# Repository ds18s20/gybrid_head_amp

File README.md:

# gybrid_head_amp
headphone amplifier using vacuum tube  and transistor in class A

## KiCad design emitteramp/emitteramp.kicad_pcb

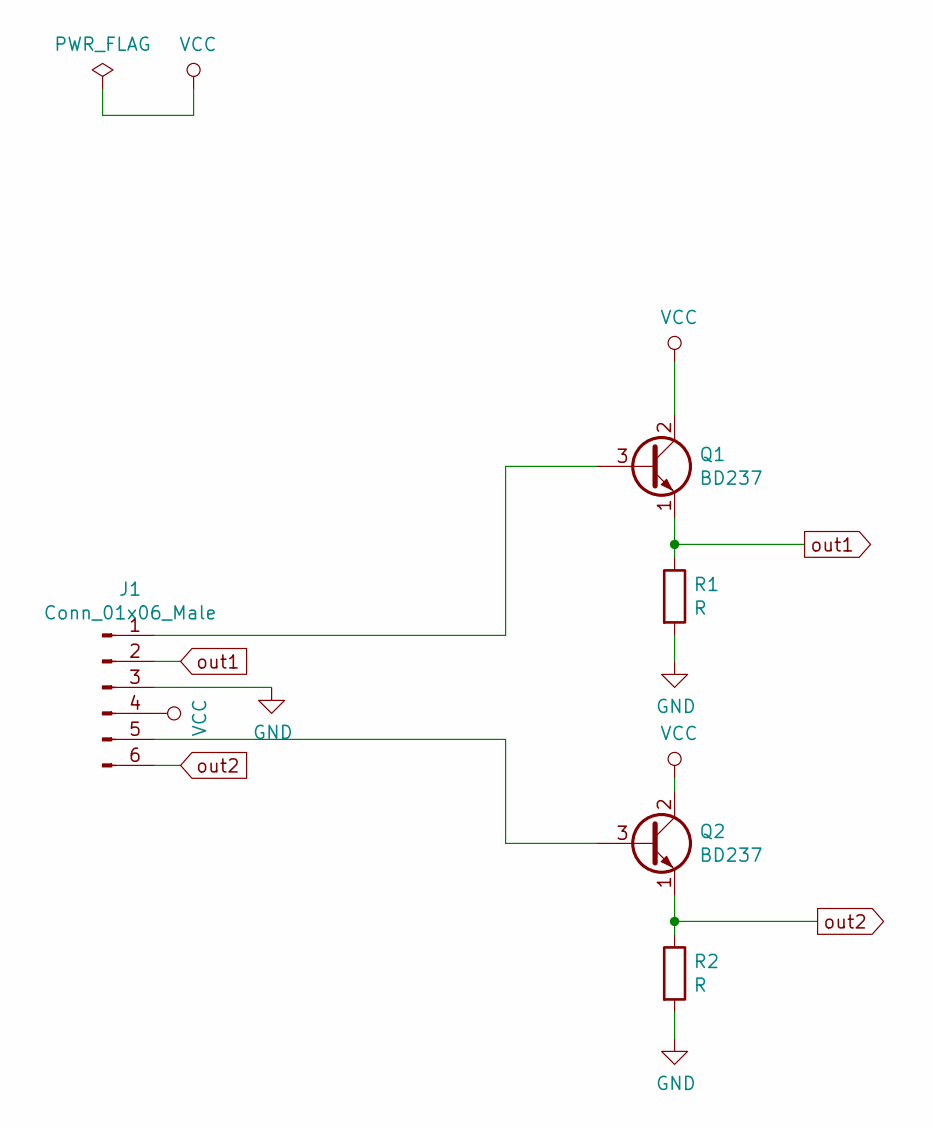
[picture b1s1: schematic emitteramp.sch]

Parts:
J1: Conn_01x06_Male; MyConn1x6
Q1, Q2: BD237; TO-126-3_Horizontal_TabDown
R1, R2: R; R_Axial_DIN0516_L15.5mm_D5.0mm_P20.32mm_Horizontal

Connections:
GND: J1.3, R1.2, R2.2
unnamed: J1.1, Q1.3 (B)
unnamed: J1.5, Q2.3 (B)
VCC: J1.4, Q1.2 (C), Q2.2 (C)
out1: J1.2, Q1.1 (E), R1.1
out2: J1.6, Q2.1 (E), R2.1

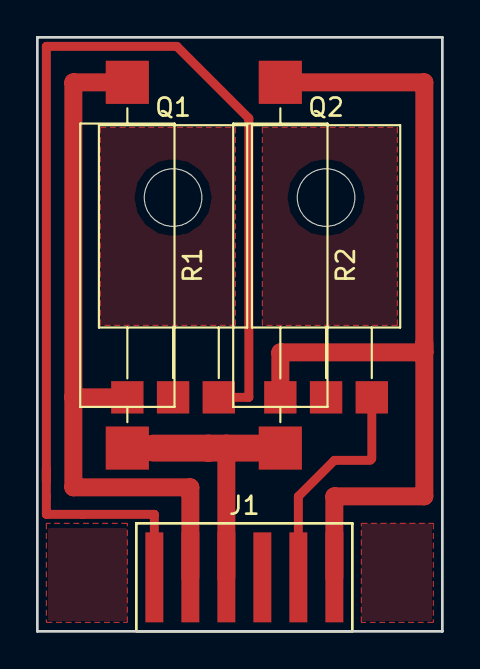
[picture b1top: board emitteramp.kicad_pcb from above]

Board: 2 copper layers, 22.5 x 33.0 mm, 5 parts (0 on the bottom side), 6 nets.

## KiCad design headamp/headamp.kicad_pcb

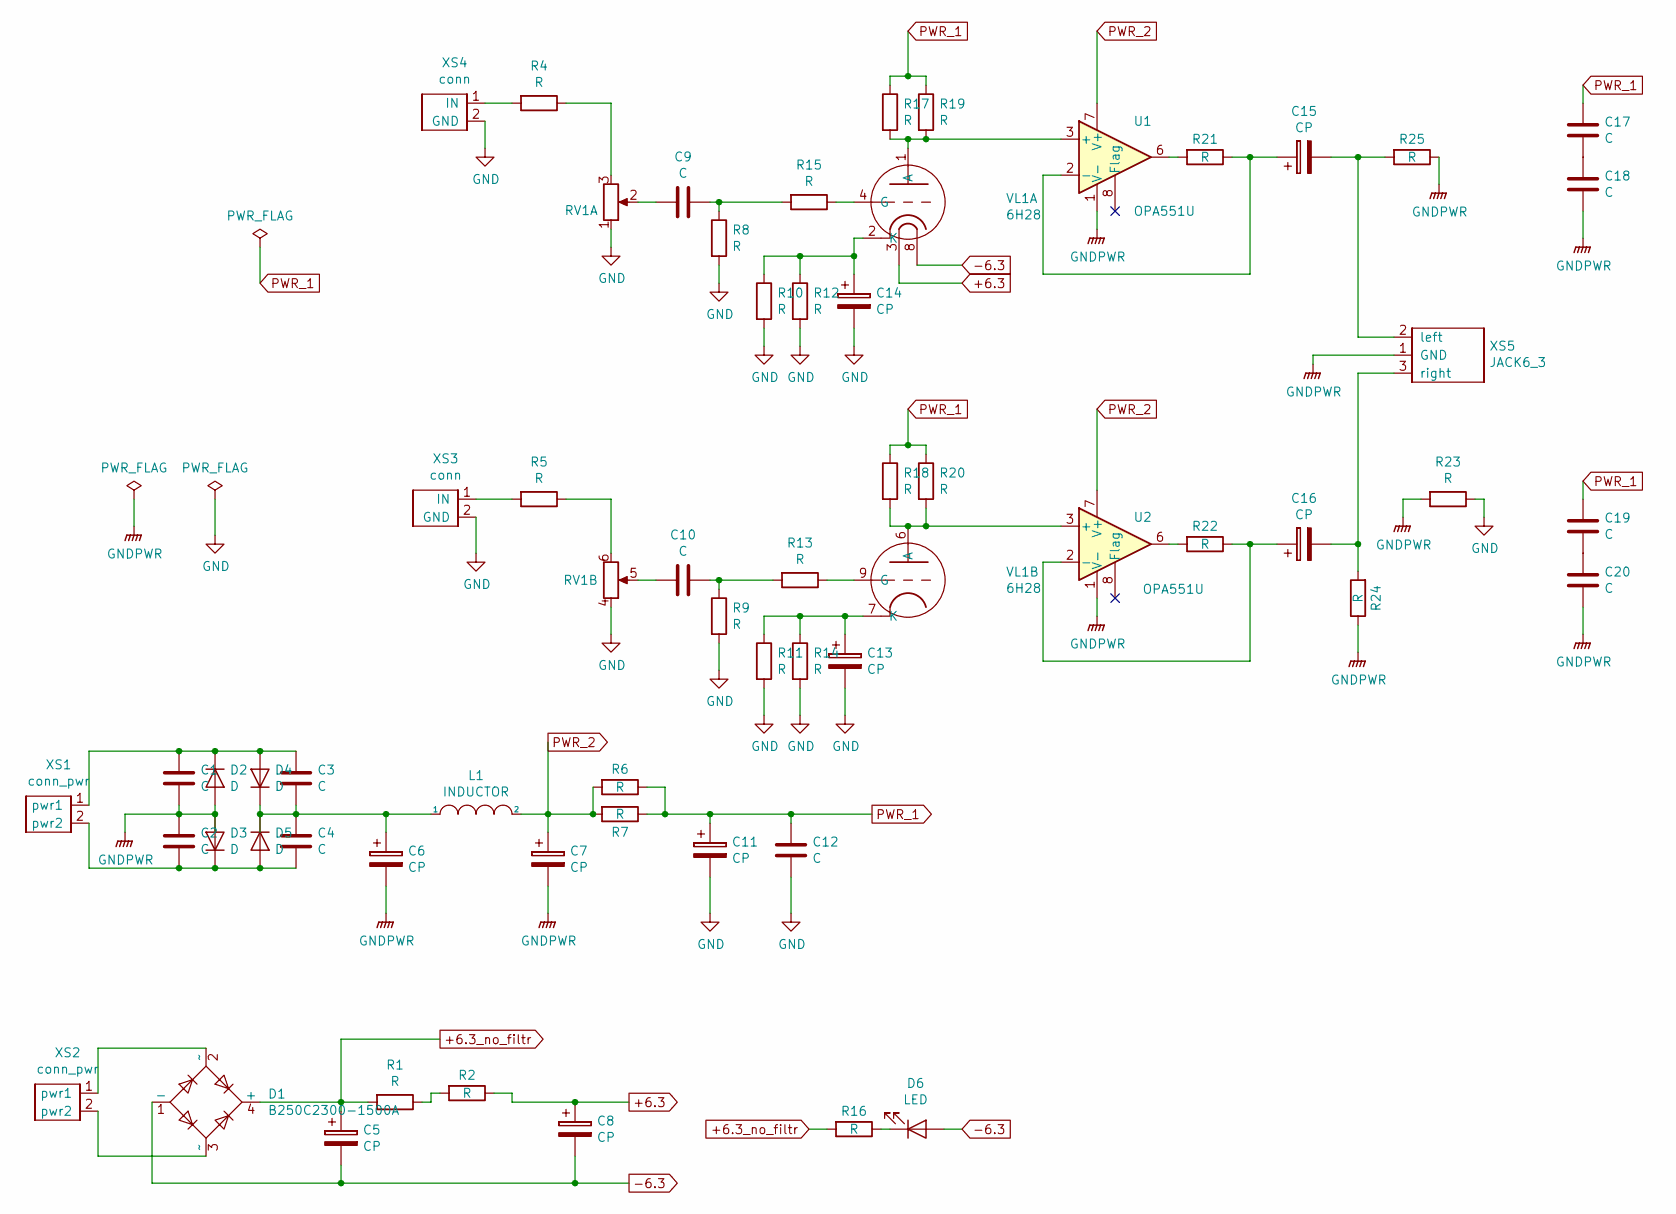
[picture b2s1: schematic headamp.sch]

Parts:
C1, C2, C3, C4, C17, C18, C19, C20: C; C_1206_3216Metric_Pad1.42x1.75mm_HandSolder
C5, C6, C8, C11, C15, C16: CP; C_Radial_D16.0mm_H25.0mm_P7.50mm
C7: CP; CP_Radial_D35.0mm_P10.00mm_SnapIn
C9, C10, C12: C; C_Disc_D7.5mm_W5.0mm_P10.00mm
C13, C14: CP; CP_Elec_8x10.5
D1: B250C2300-1500A; Diode_Bridge_Diotec_SO-DIL-Slim
D2, D3, D4, D5: D; D_SMB_Handsoldering
D6: LED; SolderWirePad_1x02_P5.08mm_Drill1.5mm
L1: INDUCTOR; SolderWirePad_1x02_P5.08mm_Drill1.5mm
R1, R2: R; R_Axial_DIN0414_L11.9mm_D4.5mm_P15.24mm_Horizontal
R4, R5, R6, R7, R8, R9, R10, R11, R12, R13, R14, R15, R16, R17, R18, R19, R20, R21, R22, R23, R24, R25: R; R_1206_3216Metric_Pad1.42x1.75mm_HandSolder
RV1: R_POT_Dual_Separate; Potentiometer_Alps_RK163_Dual_Horizontal
U1, U2: OPA551U; SOIC-8_3.9x4.9mm_P1.27mm
VL1: 6H28; 6H28_foot
XS1, XS2: conn_pwr; SolderWirePad_1x02_P3.81mm_Drill1mm
XS3, XS4: conn; SolderWirePad_1x02_P5.08mm_Drill1.5mm
XS5: JACK6_3

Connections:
+6.3: C8.1, R2.1, VL1.3
+6.3_no_filtr: C5.1, D1.4 (+), R1.2, R16.2
-6.3: C5.2, C8.2, D1.1 (-), D6.2 (A), VL1.8
GND: C11.2, C12.2, C13.2, C14.2, R8.2, R9.2, R10.2, R11.2, R12.2, R14.2, R23.1, RV1.1, RV1.4, VL1.5 (GND), XS3.2 (GND), XS4.2 (GND)
GNDPWR: C1.2, C2.1, C6.2, C7.2, C18.2, C20.2, D2.2 (A), D3.2 (A), R23.2, R24.1, R25.1, U1.1 (V-), U1.4 (V-), U1.5 (V-), U2.1 (V-), U2.4 (V-), U2.5 (V-), XS5.1 (GND)
unnamed: C1.1, C3.1, D2.1 (K), D4.2 (A), XS1.1 (pwr1)
unnamed: C2.2, C4.2, D3.1 (K), D5.2 (A), XS1.2 (pwr2)
unnamed: C3.2, C4.1, C6.1, D4.1 (K), D5.1 (K), L1.1
unnamed: C9.1, RV1.2
unnamed: C9.2, R8.1, R15.2
unnamed: C10.1, RV1.5
unnamed: C10.2, R9.1, R13.2
unnamed: C13.1, R11.1, R14.1, VL1.7 (K)
unnamed: C14.1, R10.1, R12.1, VL1.2 (K)
unnamed: C15.1, R21.1, U1.2 (-)
unnamed: C15.2, R25.2, XS5.2 (left)
unnamed: C16.1, R22.1, U2.2 (-)
unnamed: C16.2, R24.2, XS5.3 (right)
unnamed: C17.2, C18.1
unnamed: C19.2, C20.1
unnamed: D1.2 (~~), XS2.1 (pwr1)
unnamed: D1.3 (~~), XS2.2 (pwr2)
unnamed: D6.1 (K), R16.1
unnamed: R1.1, R2.2
unnamed: R4.1, RV1.3
unnamed: R4.2, XS4.1 (IN)
unnamed: R5.1, RV1.6
unnamed: R5.2, XS3.1 (IN)
unnamed: R13.1, VL1.9 (G)
unnamed: R15.1, VL1.4 (G)
unnamed: R17.2, R19.2, U1.3 (+), VL1.1 (A)
unnamed: R18.2, R20.2, U2.3 (+), VL1.6 (A)
unnamed: R21.2, U1.6
unnamed: R22.2, U2.6

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
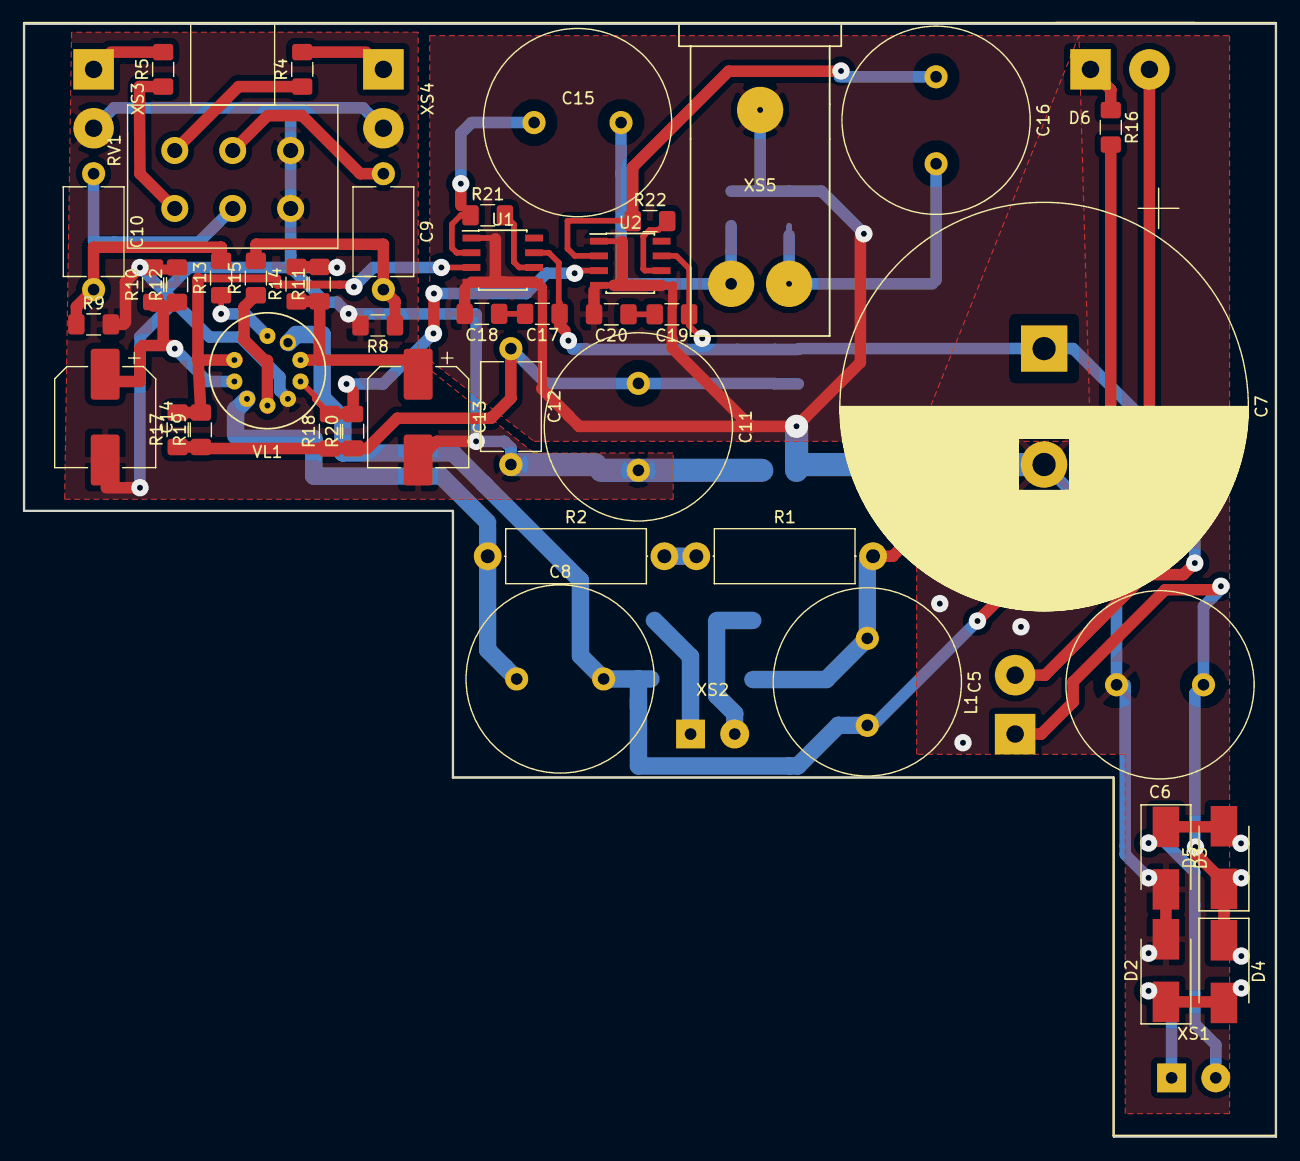
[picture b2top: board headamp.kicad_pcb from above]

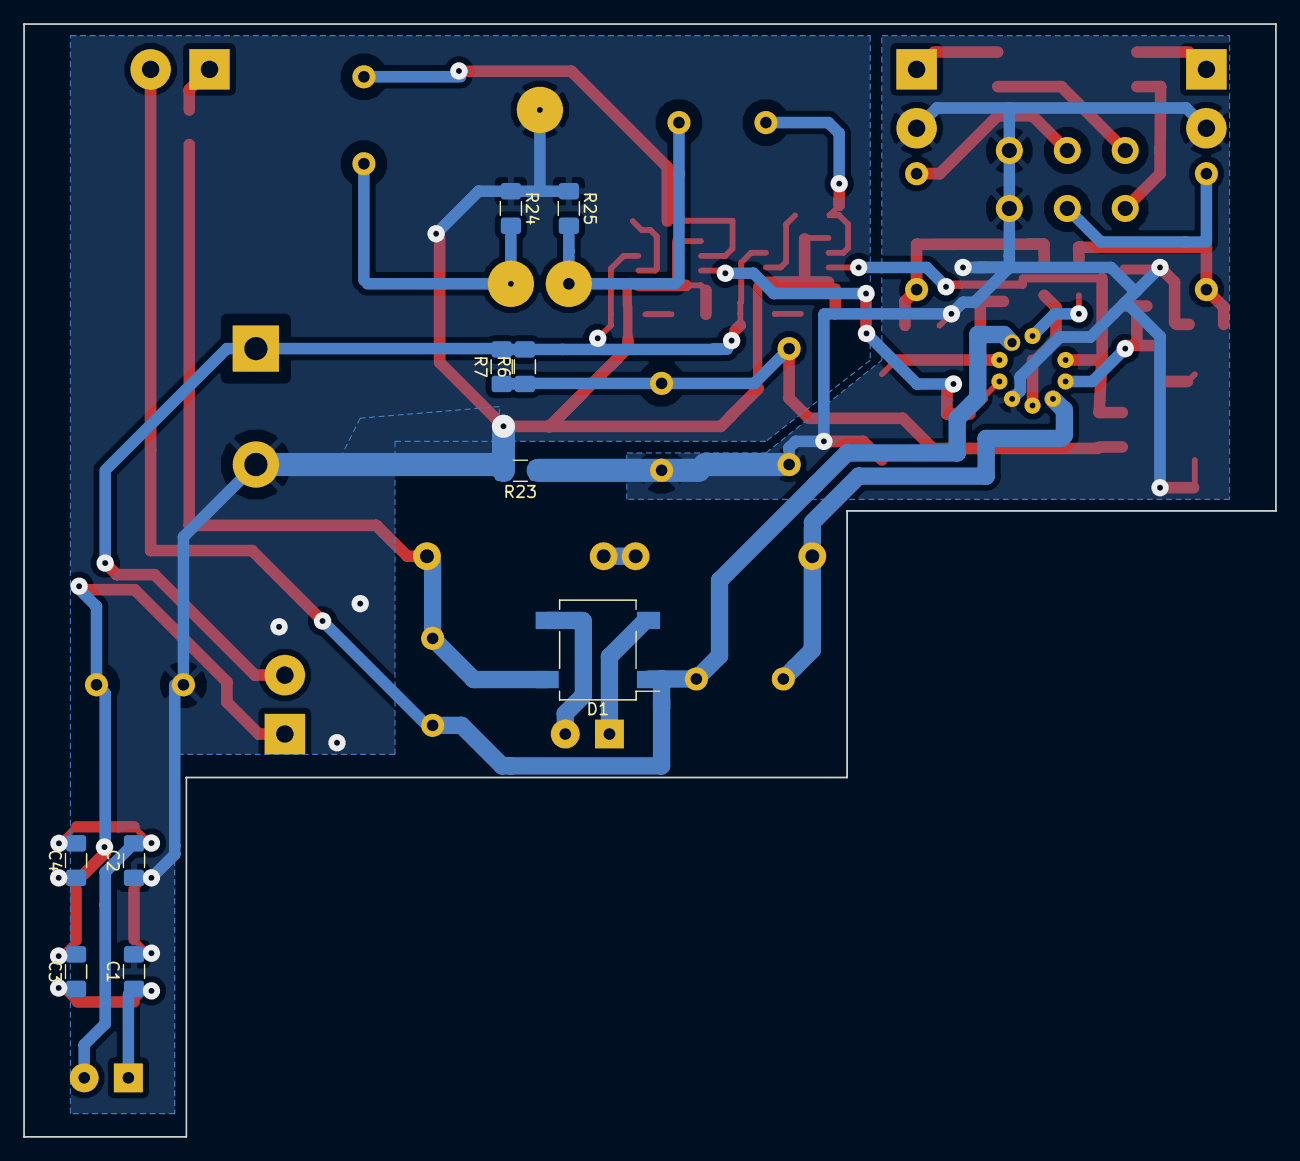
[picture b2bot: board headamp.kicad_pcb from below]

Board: 2 copper layers, 108.0 x 96.0 mm, 60 parts (10 on the bottom side), 36 nets.

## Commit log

2020-02-09 Добавили файло
2020-10-31 Чё-то исправили
